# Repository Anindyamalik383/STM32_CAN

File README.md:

# STM32_CAN
STM32F411CEU6( Black Pill) with a CAN controller IC integrated, enabling regular CAN communications to be done.
This is done by interfacing, and a  CAN TransReceiver IC, the one used here is ATA6561-GBQW-N (Atmel IC 
PA12 and PA13 are used for interfacing with the CAN Transreceiver IC

PCB DESIGN

3D View:

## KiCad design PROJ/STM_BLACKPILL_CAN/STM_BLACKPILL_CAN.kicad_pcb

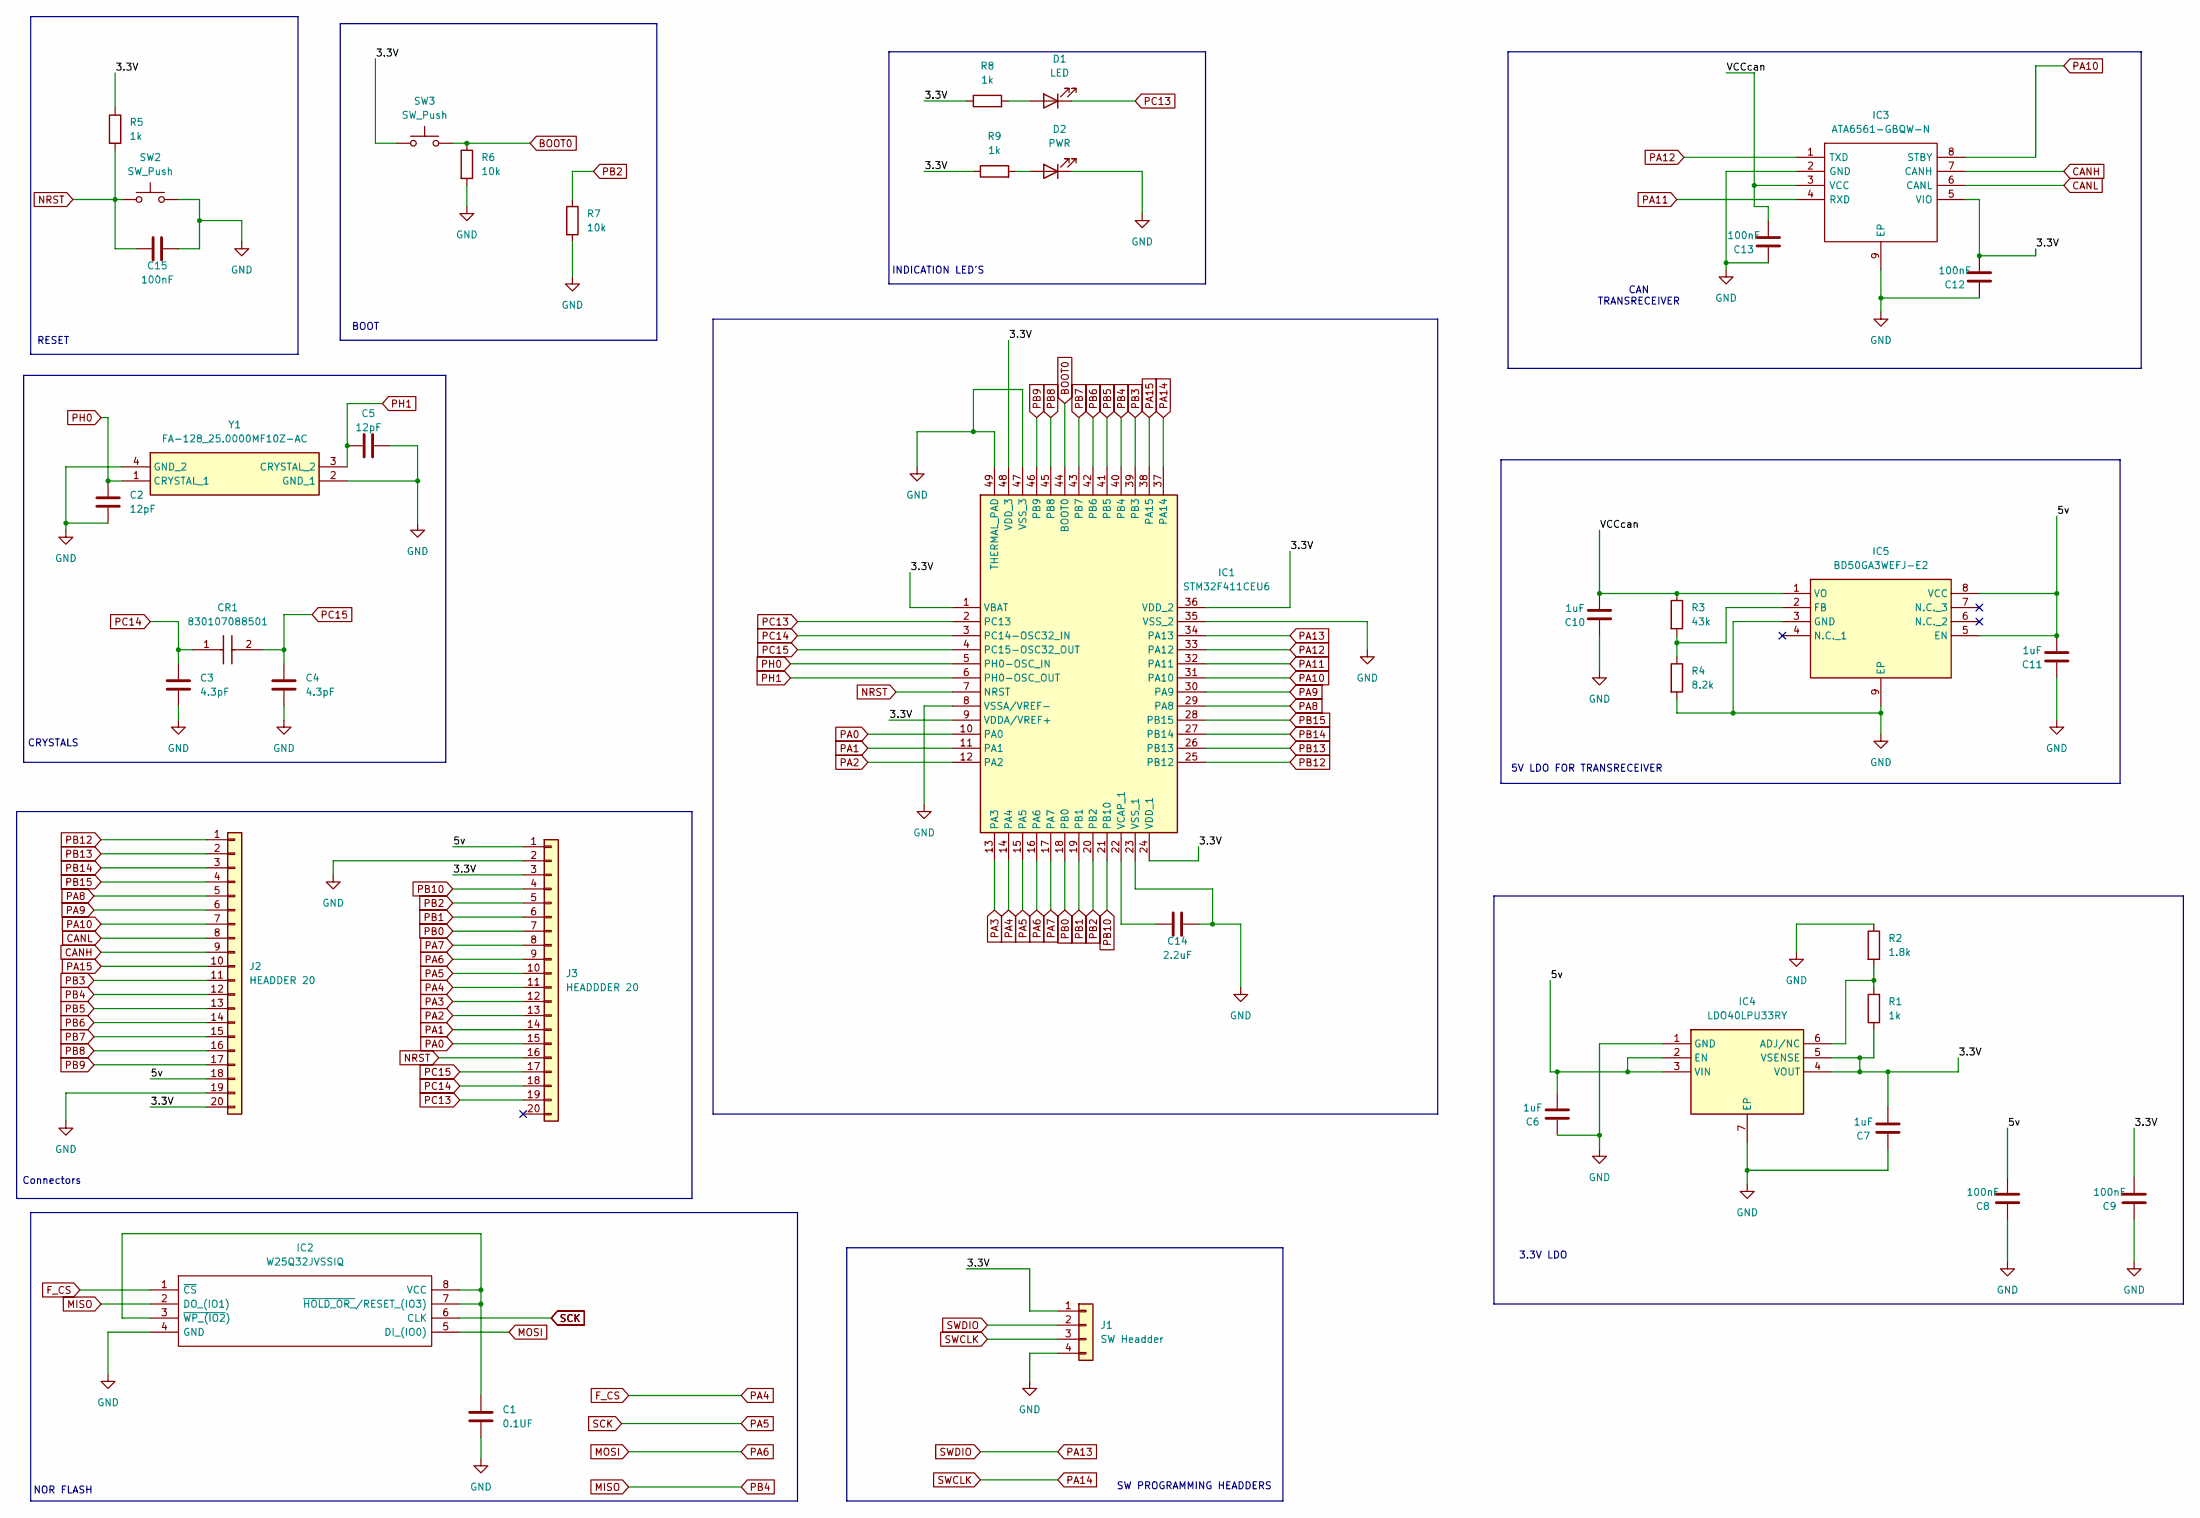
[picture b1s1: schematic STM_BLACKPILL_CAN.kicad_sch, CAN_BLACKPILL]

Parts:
C1: 0.1UF; C_0805_2012Metric
C2, C5: 12pF; C_0603_1608Metric
C3, C4: 4.3pF; C_0603_1608Metric
C6, C7, C10, C11: 1uF; C_0402_1005Metric
C8, C9, C12, C13, C15: 100nF; C_0603_1608Metric
C14: 2.2uF; C_0805_2012Metric
CR1: 830107088501; Mouser Part Number 710-830107088501
D1: LED; D_0201_0603Metric
D2: PWR; D_0201_0603Metric
IC1: STM32F411CEU6; QFN50P700X700X60-49N-D; Mouser Part Number 511-STM32F411CEU6
IC2: W25Q32JVSSIQ; SOIC127P790X216-8N; Mouser Part Number 454-W25Q32JVSSIQ
IC3: ATA6561-GBQW-N; SON65P300X300X90-9N-D; Mouser Part Number 579-ATA6561-GBQW-N
IC4: LDO40LPU33RY; SON95P300X300X90-7N-D; Mouser Part Number 511-LDO40LPU33RY
IC5: BD50GA3WEFJ-E2; SOIC127P600X100-9N; Mouser Part Number 755-BD50GA3WEFJ-E2
J1: SW Headder; PinHeader_1x04_P1.00mm_Vertical
J2: HEADDER 20; PinHeader_1x20_P1.00mm_Vertical
J3: HEADDDER 20; PinHeader_1x20_P1.00mm_Vertical
R1, R5, R8, R9: 1k; R_0402_1005Metric
R2: 1.8k; R_0402_1005Metric
R3: 43k; R_0603_1608Metric
R4: 8.2k; R_0402_1005Metric
R6, R7: 10k; R_1206_3216Metric
SW2, SW3: SW_Push; SW_SPST_CK_RS282G05A3
Y1: FA-128_25.0000MF10Z-AC; FA128240000MBW0; Mouser Part Number 732-FA-12825F10Z-AC

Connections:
/3.3V: C7.2, C9.2, C12.2, IC1.1 (VBAT), IC1.9 (VDDA/VREF+), IC1.24 (VDD_1), IC1.36 (VDD_2), IC1.48 (VDD_3), IC3.5 (VIO), IC4.4 (VOUT), IC4.5 (VSENSE), J1.1, J2.20, J3.3, R1.1, R5.1, R8.1, R9.1, SW3.1
/5v: C6.2, C8.2, C11.2, IC4.2 (EN), IC4.3 (VIN), IC5.5 (EN), IC5.8 (VCC), J2.18, J3.1
/VCCcan: C10.2, C13.2, IC3.3 (VCC), IC5.1 (VO), R3.1
BOOT0: IC1.44 (BOOT0), R6.1, SW3.2
CANH: IC3.7 (CANH), J2.9
CANL: IC3.6 (CANL), J2.8
F_CS: IC1.14 (PA4), IC2.1 (~CS), J3.11
GND: C1.2, C2.2, C3.2, C4.2, C5.2, C6.1, C7.1, C8.1, C9.1, C10.1, C11.1, C12.1, C13.1, C14.1, C15.1, D2.1 (K), IC1.8 (VSSA/VREF-), IC1.23 (VSS_1), IC1.35 (VSS_2), IC1.47 (VSS_3), IC1.49 (THERMAL_PAD), IC2.4 (GND), IC3.2 (GND), IC3.9 (EP), IC4.1 (GND), IC4.7 (EP), IC5.3 (GND), IC5.9 (EP), J1.4, J2.19, J3.2, R2.1, R4.2, R6.2, R7.2, SW2.2, Y1.2 (GND_1), Y1.4 (GND_2)
MISO: IC1.40 (PB4), IC2.2 (DO_(IO1)), J2.12
MOSI: IC1.16 (PA6), IC2.5 (DI_(IO0)), J3.9
NRST: C15.2, IC1.7 (NRST), J3.16, R5.2, SW2.1
unnamed: D1.2 (A), R8.2
unnamed: D2.2 (A), R9.2
unnamed: C14.2, IC1.22 (VCAP_1)
unnamed: C1.1, IC2.3 (~WP_(IO2)), IC2.7 (~HOLD_OR_/RESET_(IO3)), IC2.8 (VCC)
unnamed: IC4.6 (ADJ/NC), R1.2, R2.2
unnamed: IC5.2 (FB), R3.2, R4.1
PA0: IC1.10 (PA0), J3.15
PA1: IC1.11 (PA1), J3.14
PA2: IC1.12 (PA2), J3.13
PA3: IC1.13 (PA3), J3.12
PA5: IC1.15 (PA5), IC2.6 (CLK), J3.10
PA7: IC1.17 (PA7), J3.8
PA8: IC1.29 (PA8), J2.5
PA9: IC1.30 (PA9), J2.6
PA10: IC1.31 (PA10), IC3.8 (STBY), J2.7
PA11: IC1.32 (PA11), IC3.4 (RXD)
PA12: IC1.33 (PA12), IC3.1 (TXD)
PA13: IC1.34 (PA13), J1.2
PA14: IC1.37 (PA14), J1.3
PA15: IC1.38 (PA15), J2.10
PB0: IC1.18 (PB0), J3.7
PB1: IC1.19 (PB1), J3.6
PB2: IC1.20 (PB2), J3.5, R7.1
PB3: IC1.39 (PB3), J2.11
PB5: IC1.41 (PB5), J2.13
PB6: IC1.42 (PB6), J2.14
PB7: IC1.43 (PB7), J2.15
PB8: IC1.45 (PB8), J2.16
PB9: IC1.46 (PB9), J2.17
PB10: IC1.21 (PB10), J3.4
PB12: IC1.25 (PB12), J2.1
PB13: IC1.26 (PB13), J2.2
PB14: IC1.27 (PB14), J2.3
PB15: IC1.28 (PB15), J2.4
PC13: D1.1 (K), IC1.2 (PC13), J3.19
PC14: C3.1, CR1.1 (X1), IC1.3 (PC14-OSC32_IN), J3.18
PC15: C4.1, CR1.2 (X2), IC1.4 (PC15-OSC32_OUT), J3.17
PH0: C2.1, IC1.5 (PH0-OSC_IN), Y1.1 (CRYSTAL_1)
PH1: C5.1, IC1.6 (PH0-OSC_OUT), Y1.3 (CRYSTAL_2)

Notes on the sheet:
CRYSTALS
SW PROGRAMMING HEADDERS
NOR FLASH
5V LDO FOR TRANSRECEIVER
CAN TRANSRECEIVER
INDICATION LED'S
RESET
Connectors
3.3V LDO
BOOT

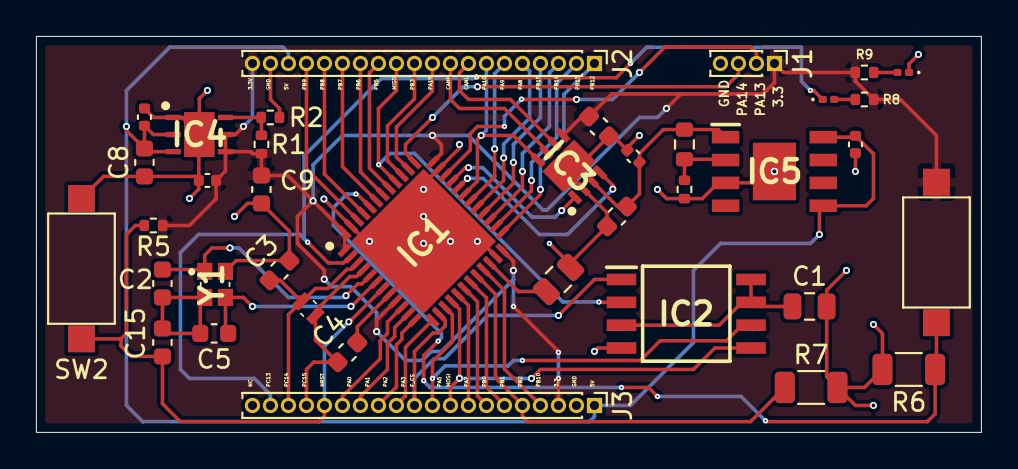
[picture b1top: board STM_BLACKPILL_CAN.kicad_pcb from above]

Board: 2 copper layers, 52.5 x 22.0 mm, 38 parts (0 on the bottom side), 50 nets.

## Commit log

2026-02-17 Uploaded all project files
2026-02-17 Update README with PCB design and 3D view
    Added PCB design and 3D view images to README.
2026-02-17 Update README with CAN TransReceiver details
    Added details about the CAN TransReceiver IC and pin usage.
